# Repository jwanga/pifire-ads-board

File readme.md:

# PiFire ADS1x15 Module PCB KiCad Files

## What is this? 

This PCB provides an easy way to add an ADS1x15 module to your PiFire build.  This allows you to have up to four different modules in your system, and can be chained together via I2C.  Use the pin header jumpers to select a unique I2C address for each of the modules in your system (default is 0x48).  The PCB provides options for JST XH connectors or screw terminals (or if you want to solder wires directly to the board you can always do that too).  Lastly, there are boxes where you can designate the value of the populated resistors, for easy reference once you've built it out.  

The design intent for this board was to make a DIY accessible PCB that can be more easily put together by the maker/enthusiast of almost any skill level.  Full size components are used in most cases and most (if not all) parts should be readily available to order online.  See the [Interactive BOM](#interactive-bom) for more details about the parts used and links to order.

### What is PiFire? 

PiFire is a SBC based Pellet Smoker Controller.  More details can be found [here](https://nebhead.github.io/PiFire) or [at the GitHub repo](https://github.com/nebhead/pifire). 

## What's in this Repository?

### KiCad Project Files 
In this repository you will find the latest KiCad design files for the  PCB.  Simply load the project file (.kicad_pro) into the KiCad software and you should be able to edit as needed.  Or if you just want to get this board made, jump to the production section below.

### Interactive BOM

There is an interactive BOM located in the [/bom](bom/) folder which details the parts and provides some pin information as well.  Use this to gather the components you may need to build this board out and refer back to it for placement help.    

[BOM + Pin Info](https://nebhead.github.io/pifire-ads-board)

_This is a standalone HTML file that was autogenerated by the excellent plugin for KiCad. See the plugin here: [https://github.com/openscopeproject/InteractiveHtmlBom](https://github.com/openscopeproject/InteractiveHtmlBom)_

### PDF of the Schematic

Preview the schematic in PDF format here: [Schematic](pifire-ads-board-schematic.pdf)

### PCB Specific Notes

#### Mounting ADS1115 Device

This intention of this PCB is to have a ADS1115 (or ADS1015) mounted to the top of this board.  You can attach this with a standard pin-header, or directly attaching with solder only.  (see the diagram below showing the ADS1115 attached in the yellow dotted line area)

#### Selecting I2C Address

In addition, you may be able to have up to four of these boards in a single system by assigning different I2C addresses to each device.  These addresses can be selected by using the pin header jumpers provided at the bottom of the board.  Simply select the address you want and close/short the solder jumper for that address.  

### JLCPCB Production Files

If you wish to get these PCBs made by JLCPCB, the production files are provided in the `/production` folder.  For convenience, the file `pifire-ads-board-production.zip` can simply be uploaded to JLCPCB to make it super easy to order boards.

Drop the zip file onto the order page, wait for it to upload then simply continue to order the board.  Optionally, select different board color, PCB quantity, surface finish, etc.  Most of the default settings should be sufficient. 

### Links to the PCBs in this family of PiFire Boards

This PCB is part of a family of PCBs that can be used together to create  a full PiFire system.  Generally speaking you need the Main Module/Board, a Relay Control Board and a Probe Device board to have a basic PiFire system.  

**Main Module/Board** (required)
* [Main Board v4.0.x](https://github.com/nebhead/pifire-main-module-nopwr)

**Relay/Fan Control Boards** (choose one)
* [Mechanical Relay Module](https://github.com/nebhead/pifire-relay-module)
* [Solid State Relay Module](https://github.com/nebhead/pifire-relay-module-SSR)
* [Solid State Relay + PWM Fan Module](https://github.com/nebhead/pifire-relay-pwm-module-ssr) - Original Design
* [Solid State Relay + PWM Fan Module Alternate](https://github.com/nebhead/pifire-relay-pwm-module-ssr-alt) - Updated Design (Designed with help from @labmonkeyrat on Discord)

**Probe Device Board** (optional)
* [ADS Board](https://github.com/nebhead/pifire-ads-board) 

### 3D Printable Enclosures/Boxes 

With all of the 3D Prints for PiFire, a higher temperature filament such as PETG should be used.  PLA generally won't stand up to the temperatures that the components may be exposed to outdoors and near a hot smoker.  

#### Enclosure

Included here is an initial revision of the enclosure for this PCB.  The current models should be considered still in development and may have alignment challenges, etc. 

Except for the mounting wings, the majority of bolts to be used with this enclosure are M3. 

* STL: [Base](/printables/PiFire-PCB-v4-ADS-Base.stl)
* STL: [Lid](/printables/PiFire-PCB-v4-ADS-Lid.stl)
* OnShape: [Enclosure Original Models](https://cad.onshape.com/documents/06ff4784dfd59b5ba448a771/w/ff8c53d96188935699d945ec/e/67f72d5e3136186b90fce856?renderMode=0&uiState=66e1183808b48b5751063bbb)

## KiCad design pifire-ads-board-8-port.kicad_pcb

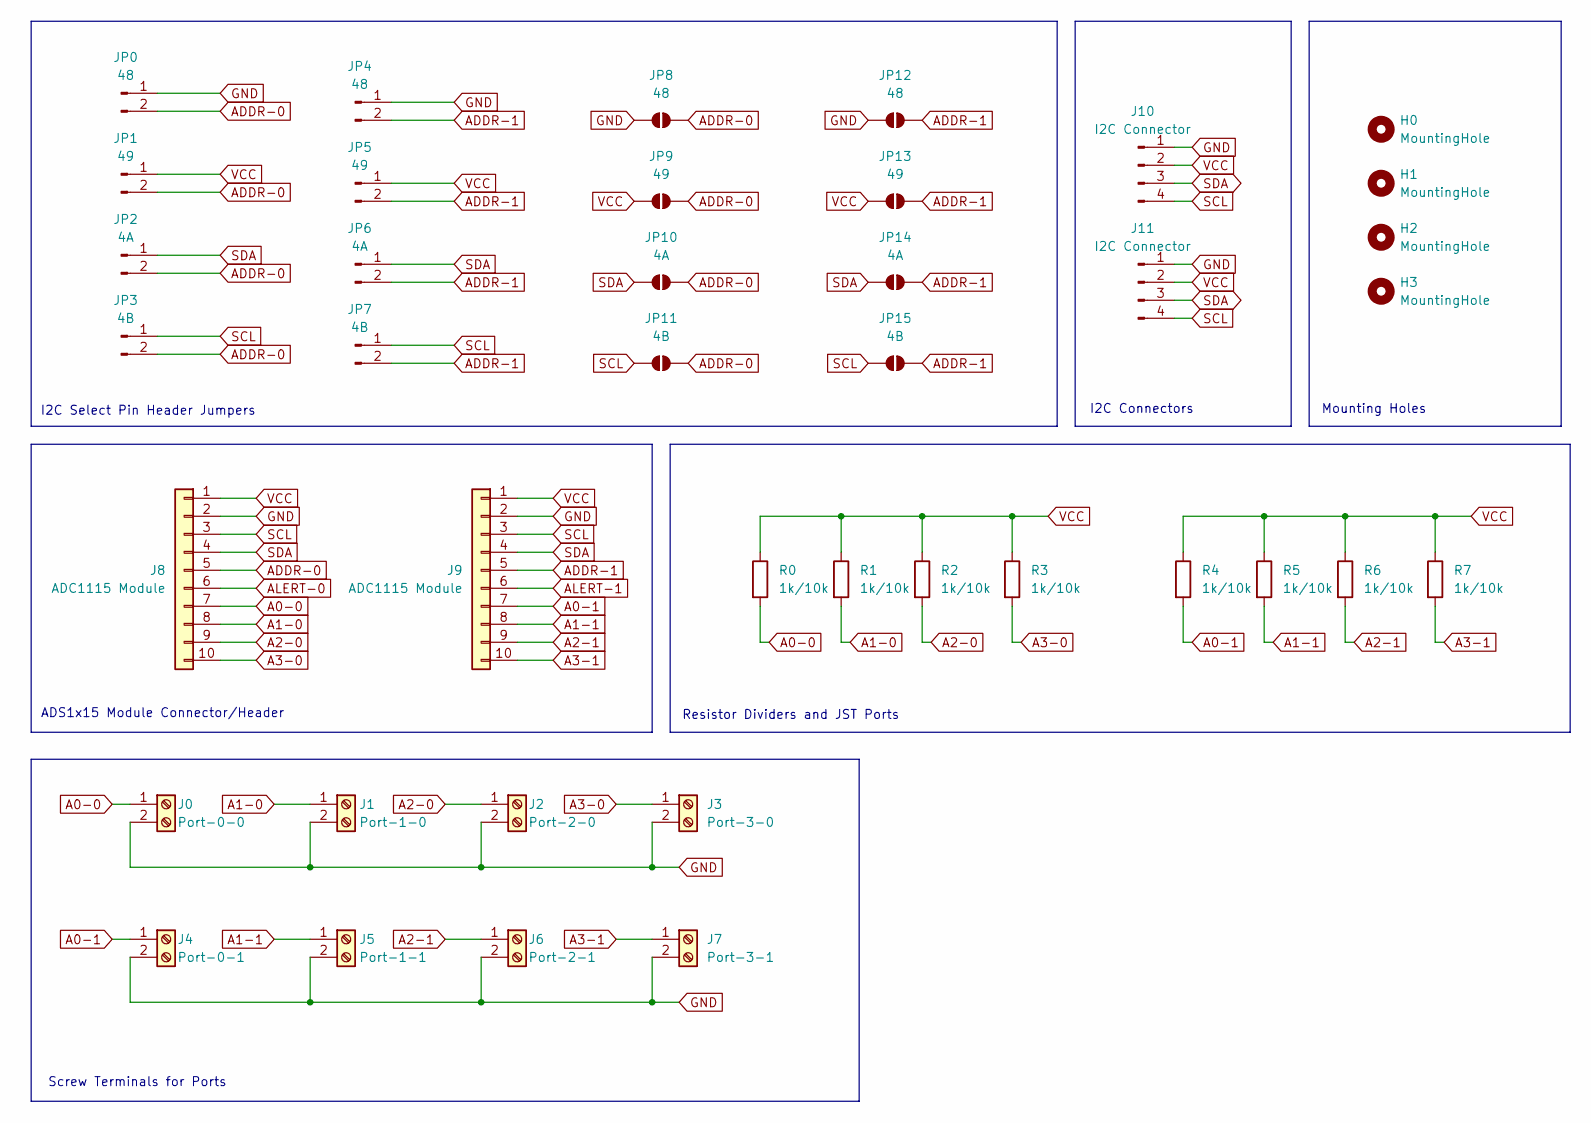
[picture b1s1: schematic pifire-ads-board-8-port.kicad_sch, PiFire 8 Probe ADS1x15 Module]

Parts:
H0, H1, H2, H3: MountingHole; MountingHole_3.2mm_M3
J0: Port-0-0; TerminalBlock_bornier-2_P5.08mm
J1: Port-1-0; TerminalBlock_bornier-2_P5.08mm
J2: Port-2-0; TerminalBlock_bornier-2_P5.08mm
J3: Port-3-0; TerminalBlock_bornier-2_P5.08mm
J4: Port-0-1; TerminalBlock_bornier-2_P5.08mm
J5: Port-1-1; TerminalBlock_bornier-2_P5.08mm
J6: Port-2-1; TerminalBlock_bornier-2_P5.08mm
J7: Port-3-1; TerminalBlock_bornier-2_P5.08mm
J8, J9: ADC1115 Module; PinHeader_1x10_P2.54mm_Vertical
J10, J11: I2C Connector; JST_XH_S4B-XH-A_1x04_P2.50mm_Horizontal
JP0, JP4: 48; PinHeader_1x02_P2.54mm_Vertical
JP1, JP5: 49; PinHeader_1x02_P2.54mm_Vertical
JP2, JP6: 4A; PinHeader_1x02_P2.54mm_Vertical
JP3, JP7: 4B; PinHeader_1x02_P2.54mm_Vertical
JP8, JP12: 48; SolderJumper-2_P1.3mm_Open_TrianglePad1.0x1.5mm
JP9, JP13: 49; SolderJumper-2_P1.3mm_Open_TrianglePad1.0x1.5mm
JP10, JP14: 4A; SolderJumper-2_P1.3mm_Open_TrianglePad1.0x1.5mm
JP11, JP15: 4B; SolderJumper-2_P1.3mm_Open_TrianglePad1.0x1.5mm
R0, R1, R2, R3, R4, R5, R6, R7: 1k/10k; R_Axial_DIN0207_L6.3mm_D2.5mm_P7.62mm_Horizontal

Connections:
A0-0: J0.1, J8.7, R0.2
A0-1: J4.1, J9.7, R4.2
A1-0: J1.1, J8.8, R1.2
A1-1: J5.1, J9.8, R5.2
A2-0: J2.1, J8.9, R2.2
A2-1: J6.1, J9.9, R6.2
A3-0: J3.1, J8.10, R3.2
A3-1: J7.1, J9.10, R7.2
ADDR-0: J8.5, JP0.2, JP1.2, JP2.2, JP3.2, JP8.2 (B), JP9.2 (B), JP10.2 (B), JP11.2 (B)
ADDR-1: J9.5, JP4.2, JP5.2, JP6.2, JP7.2, JP12.2 (B), JP13.2 (B), JP14.2 (B), JP15.2 (B)
ALERT-0: J8.6
ALERT-1: J9.6
GND: J0.2, J1.2, J2.2, J3.2, J4.2, J5.2, J6.2, J7.2, J8.2, J9.2, J10.1, J11.1, JP0.1, JP4.1, JP8.1 (A), JP12.1 (A)
SCL: J8.3, J9.3, J10.4, J11.4, JP3.1, JP7.1, JP11.1 (A), JP15.1 (A)
SDA: J8.4, J9.4, J10.3, J11.3, JP2.1, JP6.1, JP10.1 (A), JP14.1 (A)
VCC: J8.1, J9.1, J10.2, J11.2, JP1.1, JP5.1, JP9.1 (A), JP13.1 (A), R0.1, R1.1, R2.1, R3.1, R4.1, R5.1, R6.1, R7.1

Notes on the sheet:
Screw Terminals for Ports
ADS1x15 Module Connector/Header
I2C Select Pin Header Jumpers
Resistor Dividers and JST Ports
Mounting Holes
I2C Connectors

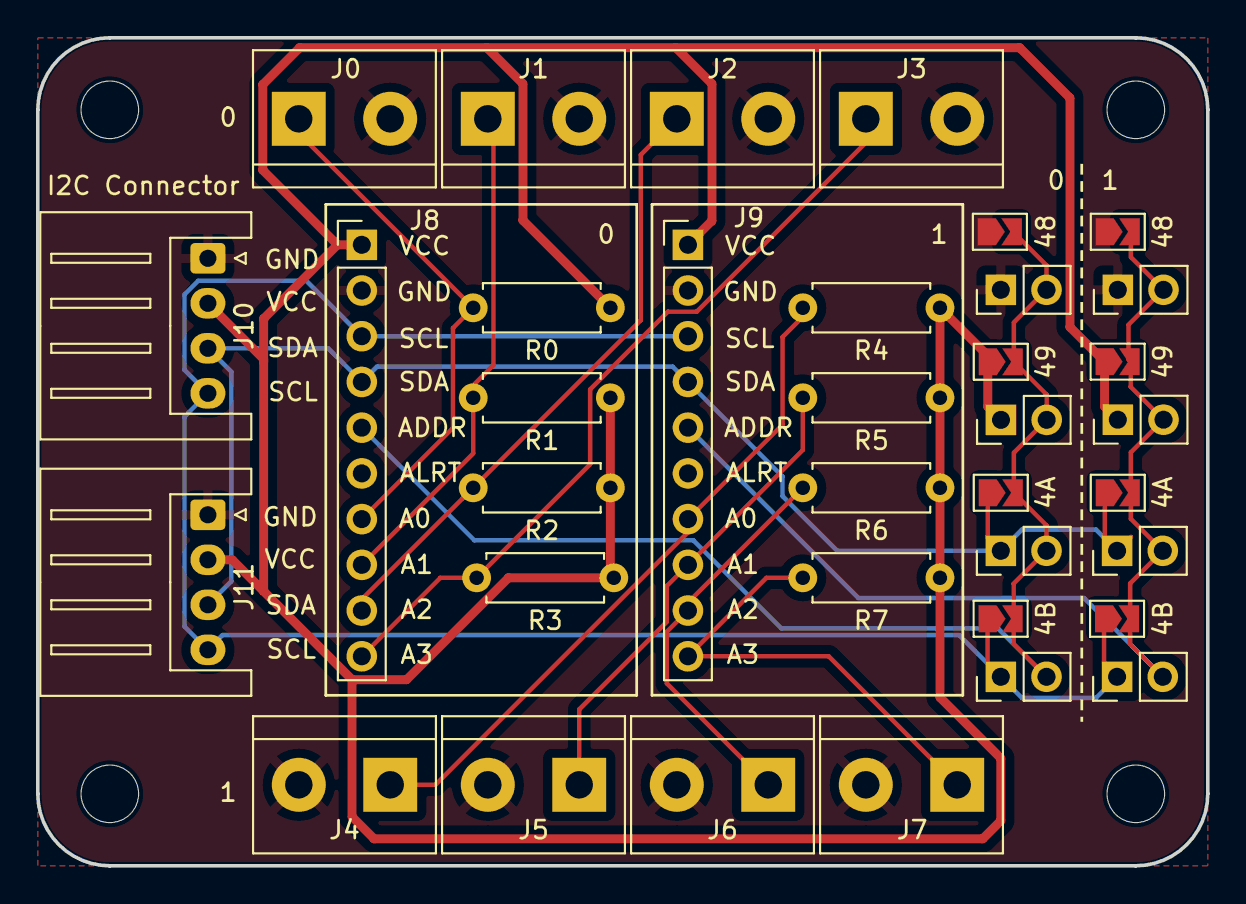
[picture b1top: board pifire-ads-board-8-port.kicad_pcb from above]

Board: 2 copper layers, 65.0 x 46.0 mm, 40 parts (0 on the bottom side), 14 nets.

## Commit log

2024-12-06 Added 2nd ad1115
